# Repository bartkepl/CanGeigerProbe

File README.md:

# CanGeigerProbe
## Sonda promieniowania G-M z interfejsem CAN

Polowa sonda promieniowania jonizującego z miniaturową lampą Geigera-Müllera, komunikująca się cyfrowo przez **CAN 2.0B**. Zaprojektowana jako element rozproszonego systemu pomiarowego: wąska sonda cylindryczna w obudowie aluminiowej, jedno złącze M12, micropower, odporność EMC klasy przemysłowej.

> **Status:** schemat (6 arkuszy hierarchicznych) i layout PCB zakończone, pliki produkcyjne wygenerowane — przed zamówieniem prototypu. Firmware na etapie szkieletu bring-up.

Inspiracja: sondy Polon-Alfa (DPO-G, ZR-1) — jedna sonda, cyfrowe wyjście do jednostki nadrzędnej, wymienność lamp.

---

## Płytka

Render 3D aktualnego layoutu (KiCad 10, 4 warstwy, 86 × 29.9 mm, wycięcie pod złącze M12 na lewej krawędzi):

| Góra (TOP) | Dół (BOTTOM) |
|---|---|
|  |  |

Cała elektronika mieści się na jednej stronie; spód pozostaje niemal pusty — rezerwa na strefę HV (widoczny prostokąt creepage z pinami anody i lampy), pole lutownicze wyprowadzeń transformatora oraz uziemienie obudowy. Transformator flybacka jest **off-board** (skręcona para przewodów 4–6 cm).

---

## Najważniejsze cechy

- **Programowalne HV 350–550 V** — jedna sonda obsługuje wiele typów lamp, setpoint ustawiany przez CAN bez zmian sprzętowych.
- **Micropower** — pobór idle rzędu setek µA dzięki buckowi LT8606 (Iq 2.5 µA), MCU w Stop 2 i podwójnemu wybudzaniu (RTC + aktywność magistrali).
- **Flyback sterowany deterministycznie z MCU** — brak dedykowanego kontrolera PWM; TIM2 generuje burst, ADC mierzy HV, firmware zamyka pętlę bang-bang.
- **CAN 2.0B (29-bit ID)** z wybudzaniem na aktywność magistrali, 125 kbit/s – 1 Mbit/s.
- **Przełączalna terminacja CAN** — split 2×59 Ω + 4.7 nF załączany dwoma PhotoMOS-ami z GPIO (sonda na końcu linii vs. w środku, bez zwór).
- **Pomiar własnego poboru prądu** — INA186 A4 (G=200) + shunt 0.5 Ω, rozdzielczość ~2 µA/count; diagnostyka linii i weryfikacja budżetu mocy.
- **Zegar czasu rzeczywistego z podtrzymaniem** — MCP79410 + ogniwo MS621FE; kwarc 32.768 kHz służy też do kalibracji wewnętrznego MSI w STM32.
- **Wymienność lamp** — rezystor gaszący `R12` na PCB dobierany pod konkretną lampę.
- **Odporność EMC** — kaskadowa ochrona coarse→fine (GDT 3-elektrodowe / TVS / CMC / podwójne ferryty), testy IEC 61000-4-2/-4/-5.
- **Obudowa aluminiowa IP67**, złącze M12 5-pin A-coded (standard CANopen CiA 303-1).

---

## Specyfikacja

| Parametr | Wartość |
|----------|---------|
| Detektor bazowy | DOI-80 (~400 V) |
| Zakres HV | 350–550 V, programowalny |
| Wielkości mierzone | CPS/CPM, moc dawki, dawka skumulowana, prąd zasilania, alarmy progowe |
| Interfejs | CAN 2.0B (extended ID), 125k / 250k / 500k / 1 Mbit |
| Zasilanie | 7–32 V DC, wspólna masa (bez izolacji galwanicznej) |
| Pobór idle | ~200 µA @ 12 V |
| Pobór aktywny | ~3.7 mA @ 12 V (chwilowo), do ~20 mA przy TX CAN @ 7 V |
| Ochrona EMC | ESD ±8 kV, Burst ±2 kV, Surge ±2 kV |
| Złącze | M12 5-pin A-coded (1=Vin, 2=GND, 3=CAN_H, 4=CAN_L, 5=Earth) |
| PCB | 4 warstwy, 86 × 29.9 mm, grubość 1.59 mm |
| Obudowa | Aluminiowa cylindryczna Ø wewn. 25 mm, IP67 |

---

## Kompatybilne lampy G-M

Zmiana lampy = zmiana programowa HV + dobór rezystora gaszącego `R12`.

| Lampa | HV nom. | R12 (quench) | Uwaga |
|-------|---------|--------------|-------|
| **DOI-80** | ~400 V | **5.1 MΩ** | domyślna |
| SBM-20 / STS-5 | 400 V | 4.7 MΩ | drop-in z DOI-80 |
| SBM-19 | ~400 V | 5.1 MΩ | |
| J305 / M4011 | ~400 V | 4.7 MΩ | lampy chińskie |
| LND712 | 500 V | 10 MΩ | wymaga wyższego HV |

Rezystor HV w obudowie 1206 (HVC1206) — lutowany wg używanej lampy.

---

## Architektura

```
M12 Vin (7-32V) ─▶ Ochrona (GDT+TVS+ferryt) ─▶ shunt 0.5Ω ─▶ LT8606 buck ─▶ +5V ─┬─▶ ATA6561 (CAN)
                                                    │                              │
                                                 INA186 ─▶ ADC                     ├─▶ MCP1700 LDO ─▶ +3.3V ─▶ STM32L432
                                                                                   │                              │
                                                                                   │                     MCP79410 RTC + BT1
                                                                                   │
                                                                                   └─▶ Flyback (Q1 + T1 P18/11) ─▶ +HV
                                                                                                                    │
   Lampa G-M ◀─ R12 (quench) ◀─ dzielnik HV 1GΩ:1MΩ ◀─────────────────────────────────────────────────────────────┘
        │
        └─▶ dzielnik pojemnościowy ─▶ COMP1 (próg z DAC1) ─▶ LPTIM (zliczanie w Stop 2)
```

Kluczowa cecha: **wspólna masa** (star ground), izolacja zapewniona wyłącznie przez TVS/GDT; `Earth` (obudowa) oddzielona od `GND` sygnałowej i łączona tylko przez Y-cap 1 nF/2 kV. Flyback „śpi" i budzi się kilka razy na sekundę — stąd pobór na poziomie µA.

### Arkusze schematu

| Arkusz | Plik | Zawartość |
|--------|------|-----------|
| root | [geiger_probe.kicad_sch](pcb/geiger_probe.kicad_sch) | połączenia hierarchiczne |
| PWR | [pwr.kicad_sch](pcb/pwr.kicad_sch) | buck LT8606, LDO MCP1700, INA186, dzielnik VIN_SENSE |
| MCU | [mcu.kicad_sch](pcb/mcu.kicad_sch) | STM32L432, RTC MCP79410, kwarc 32k, SWD (Tag-Connect) |
| HV | [hv.kicad_sch](pcb/hv.kicad_sch) | flyback (trafo, Q1, snubber RCD), dzielnik HV, detektor GM + shaper |
| CAN_BUS | [can_bus.kicad_sch](pcb/can_bus.kicad_sch) | ATA6561, terminacja PhotoMOS |
| PROTECTION | [prot.kicad_sch](pcb/prot.kicad_sch) | ochrona Vin i CAN, złącze M12 |

Wyrenderowane PDF-y: [schemat](prod/sch/geiger_probe.pdf) · [PCB](prod/pcb/geiger_probe.pdf) · [interaktywny BOM](prod/ibom/geiger_probe_ibom.html).

---

## Kluczowe komponenty

| Blok | Element | Uwaga |
|------|---------|-------|
| Buck | LT8606IDC#TRPBF | DFN-8, Iq 2.5 µA (zawsze Burst Mode), Vref FB 0.778 V — jedyny element spoza TME |
| LDO 3.3 V | MCP1700-3302E/MB | SOT-89, Iq 1.6 µA |
| Current sense | INA186A4IDCKR + 0.5 Ω | 40 V CM, G=200, pin EN — pomiar poboru sondy |
| MCU | STM32L432KCU6 | bxCAN, LPTIM, COMP1, TIM2, ADC, DAC1 |
| RTC | MCP79410-I/MS + MS621FE-FL11E | RTC/EEPROM I2C z podtrzymaniem, kwarc 32.768 kHz |
| CAN | ATA6561-GAQW-N | zamiennik TJA1042 dostępny w TME |
| Terminacja CAN | 2× GAQY212GS + 2× 59 Ω + 4.7 nF | split przełączalny, sterowany BSS138 |
| Transformator | własny P18/11-3F3, 17:510 | nawijany ręcznie, off-board |
| Klucz flyback | DMN3404L | 30 V, snubber RCD (BAV21WS) clamp do +5 V |
| Dioda HV | STTH112A | 1200 V |
| Dzielnik HV | 2× HVC1206 500 MΩ | /1001, ochrona ADC diodami BAV199 |
| Ochrona Vin | 3R090-5S (GDT) + SMBJ33CA + PMEG6030EP + 2× SMBJ36A | kaskada coarse→fine, podwójny ferryt BLM31 |
| Ochrona CAN | 3R090-5S + CDSOT23-T24CAN + ACT45B-510 | GDT, dedykowany TVS, CMC |

Pełna lista: [prod/bom/](prod/bom/) (generowana z KiCad, nietrackowana w git). Szacunkowy koszt kompletu: **~160–200 zł**.

---

## Transformator (DIY)

Najbardziej „ręczna" część projektu — rdzeń kubełkowy **P18/11-3F3**, mocowany śrubą **M2 A2 (nierdzewna, niemagnetyczna!)** z podkładkami nylonowymi chroniącymi kruchy ferryt.

- Pierwotne: **17 zw** drut 0.30 mm CuL
- Wtórne: **510 zw** drut 0.10 mm CuL (przekładnia 1:30)
- Szczelina: Kapton 100 µm między połówkami
- Parametry docelowe: Lp ≈ 75 µH, Ls ≈ 67 mH, leakage < 1.5 µH, izolacja P/S > 1 GΩ

Zasilany z **+5 V** (nie z Vin), snubber RCD clamp do +5 V — recykling energii rozproszenia, Vds ~20 V, cichy EMC. Procedura nawijania, obliczenia i testy (hi-pot 1 kV/60 s) — patrz dokumentacja projektowa.

---

## Firmware

Projekt STM32CubeIDE w [firmware/CanGeigerProbe/](firmware/CanGeigerProbe/) — na razie szkielet wygenerowany z CubeMX ([CanGeigerProbe.ioc](firmware/CanGeigerProbe/CanGeigerProbe.ioc)) z inicjalizacją ADC1, CAN1, COMP1, DAC1, I2C1 i TIM2. Logika aplikacji (pętla HV, zliczanie w Stop 2, protokół CAN) do napisania.

---

## Roadmap

- [x] **Faza 1** — projekt: topologia, dobór komponentów, obliczenia, EMC, budżet mocy
- [ ] **Faza 2** — prototyp transformatora (nawinięcie, strojenie, testy)
- [x] **Faza 3** — schemat i layout PCB w KiCad (strefy HV / analog / cyfrowe), pliki produkcyjne wygenerowane
- [ ] **Faza 3b** — zamówienie PCB, montaż sekcyjny, bring-up sprzętowy
- [ ] **Faza 4** — firmware (LPTIM+COMP w Stop 2, pętla HV, bxCAN + wake-up, RTC/kalibracja MSI, current-sense, protokół)
- [ ] **Faza 5** — kalibracja HV per lampa, kalibracja CPS→µSv/h (Cs-137), testy EMC
- [ ] **Faza 6** — mechanika: obudowa Al, montaż M12, testy IP67

---

## Struktura repozytorium

```
.
├── media/          # rendery 3D płytki
├── pcb/            # projekt KiCad 10 (schemat hierarchiczny, PCB, biblioteki lokalne, modele 3D)
├── prod/           # pliki produkcyjne: gerbery (.zip), PDF schematu i PCB, interaktywny BOM
├── sim/            # symulacje LTspice (flyback HV, LT8606)
└── firmware/       # projekt STM32CubeIDE (STM32L432, szkielet bring-up)
```

Pliki produkcyjne generowane są jobsetami KiCad: [gen_prod.kicad_jobset](pcb/gen_prod.kicad_jobset) (PDF + BOM), [gen_gerber.kicad_jobset](pcb/gen_gerber.kicad_jobset) (gerbery + wiertła), [gen_media.kicad_jobset](pcb/gen_media.kicad_jobset) (rendery 3D).

---

## Referencje

- Analog Devices **CN-0536** — Geiger Counter Circuit (odczyt z anody, dzielnik pojemnościowy, komparator)
- STM32L432: RM0394, DS11453; bxCAN: AN2606, AN5028
- LT8606 (Analog Devices), MCP1700 / MCP79410 / ATA6561 (Microchip), INA186 (TI)
- Ferroxcube P18/11, materiał 3F3; EPCOS/TDK B65651/B65652
- IEC 61000-4-2/-4/-5; EN 61326-1; EN 61000-6-2
- CAN 2.0B: ISO 11898-1/-2; CANopen CiA 301, CiA 303-1; M12: IEC 61076-2-101
- Polski podręcznik metrologii promieniowania — układy pracy liczników DOI/BOI/GOI

---

## Licencja

MIT

---

> ⚠️ **Uwaga bezpieczeństwa:** urządzenie generuje napięcie ~350–550 V. Zachowaj ostrożność przy uruchamianiu i pomiarach obwodów HV.

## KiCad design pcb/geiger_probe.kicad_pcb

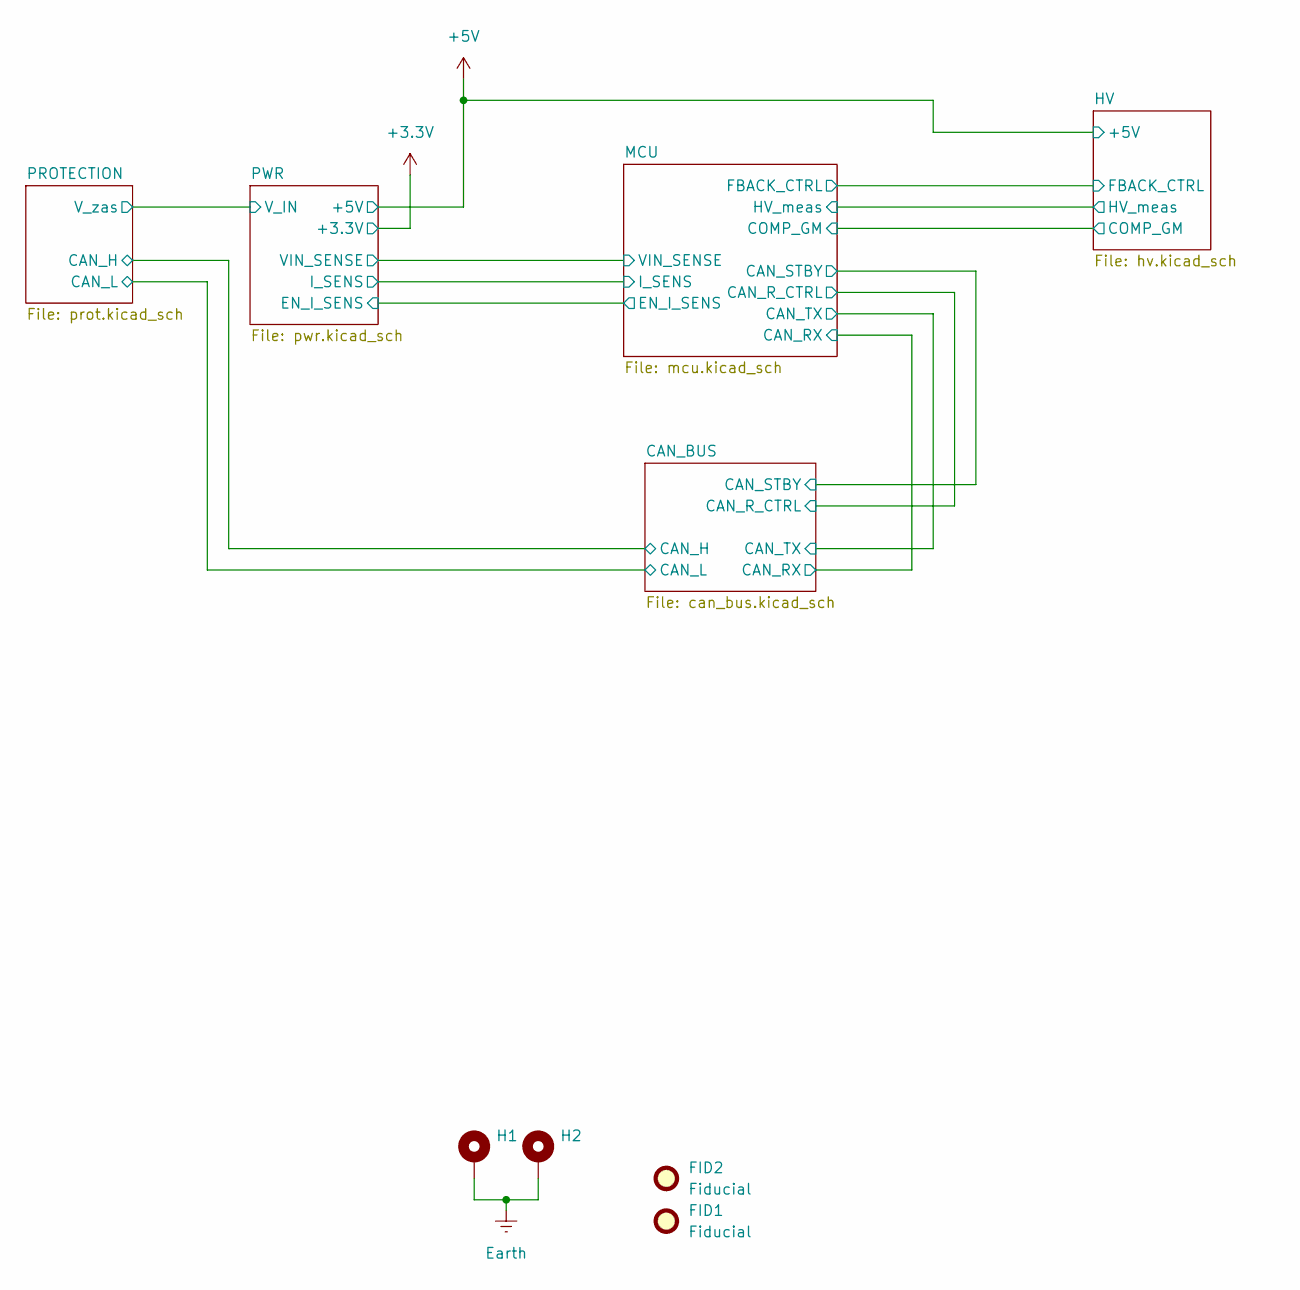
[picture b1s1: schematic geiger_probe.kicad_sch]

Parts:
FID1, FID2: Fiducial; Fiducial_0.5mm_Mask1mm
H1, H2: MountingHole_Pad; Sinhoo_SMTSO-M2_Hole3.8mm_Pad6.2mm

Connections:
Earth: H1.1 (1_1), H2.1 (1_1); also elsewhere on the board

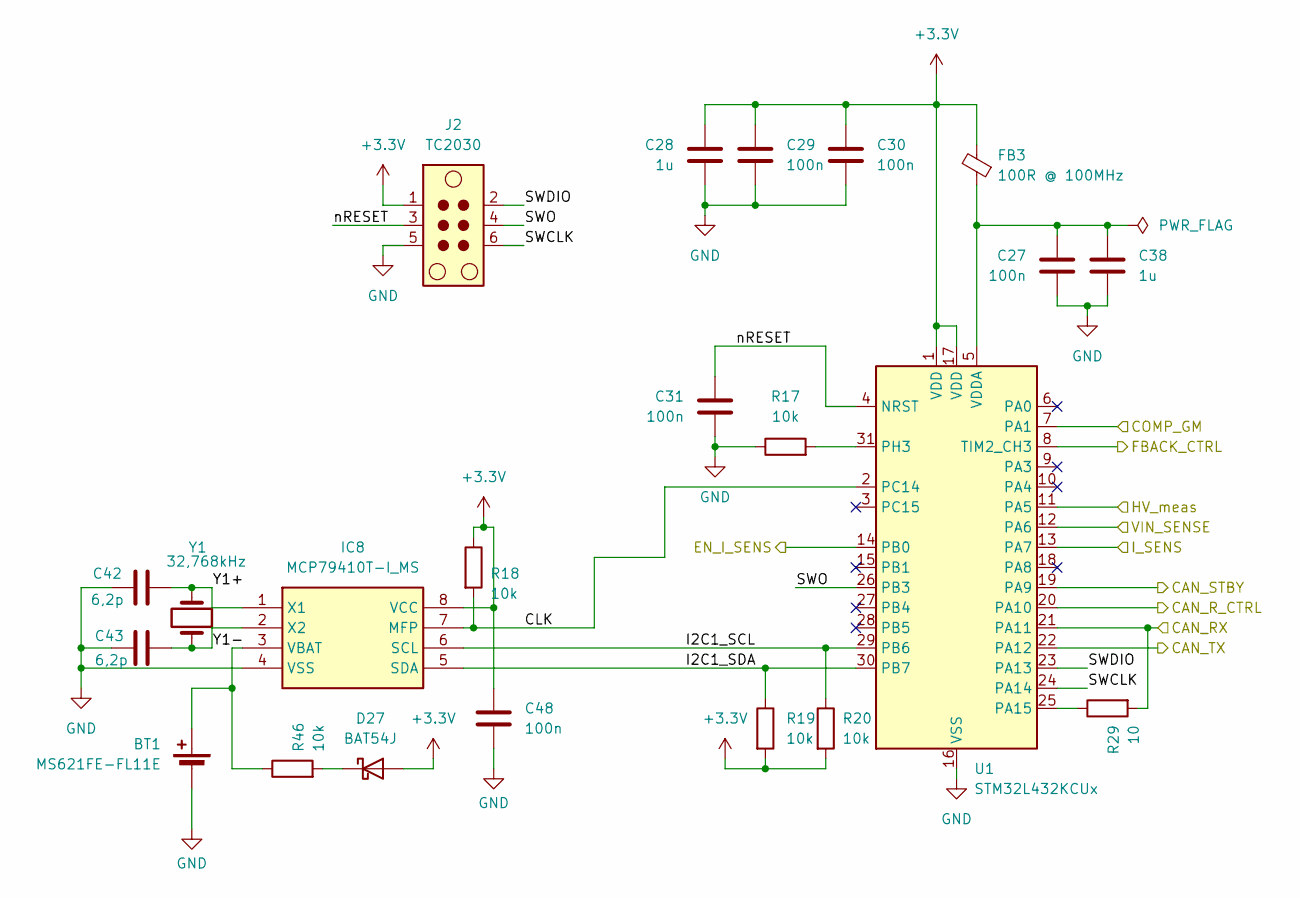
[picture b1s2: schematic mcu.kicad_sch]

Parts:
BT1: MS621FE-FL11E; BAT_MS621FE-FL11E; MPN MS621FE-FL11E
C27, C29, C30, C31, C48: 100n; C_0603_1608Metric; MPN TCC0603X7R104K500CT; LCSC C282519
C28, C38: 1u; C_0603_1608Metric; MPN 0603X105K500NT; LCSC C157684
C42, C43: 6,2p; C_0402_1005Metric; MPN CC0402CRNPO9BN6R2; LCSC C325456
D27: BAT54J; D_SOD-323F; MPN BAT54J,115
FB3: 100R @ 100MHz; L_0603_1608Metric; MPN MH1608-101Y
IC8: MCP79410T-I_MS; SOP65P490X110-8N; MPN MCP79410-I/MS
J2: TC2030; Tag-Connect_TC2030-IDC-NL_2x03_P1.27mm_Vertical
R17, R18, R19, R20, R46: 10k; R_0603_1608Metric; MPN RMS06FT1002; LCSC C209013
R29: 10; R_0603_1608Metric; MPN 0603WAF100JT5E; LCSC C22859
U1: STM32L432KCUx; QFN-32-1EP_5x5mm_P0.5mm_EP3.1x3.1mm_ThermalVias; MPN STM32L432KCU6
Y1: 32,768kHz; Crystal_SMD_MicroCrystal_CC7V-T1A-2Pin_3.2x1.5mm; MPN WTL1X80739BEL

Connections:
+3.3V: C28.1, C29.2, C30.2, C48.1, D27.2 (A), FB3.2, IC8.8 (VCC), J2.1, R18.1, R19.2, R20.2, U1.1 (VDD), U1.17 (VDD); also elsewhere on the board
/CAN_BUS/CAN_RX: R29.2, U1.21 (PA11); also elsewhere on the board
/CAN_BUS/CAN_R_CTRL: U1.20 (PA10); also elsewhere on the board
/CAN_BUS/CAN_STBY: U1.19 (PA9); also elsewhere on the board
/CAN_BUS/CAN_TX: U1.22 (PA12); also elsewhere on the board
/HV/COMP_GM: U1.7 (PA1); also elsewhere on the board
/HV/FBACK_CTRL: U1.8 (TIM2_CH3); also elsewhere on the board
/HV/HV_meas: U1.11 (PA5); also elsewhere on the board
/MCU/CLK: IC8.7 (MFP), R18.2, U1.2 (PC14)
/MCU/EN_I_SENS: U1.14 (PB0); also elsewhere on the board
/MCU/I2C1_SCL: IC8.6 (SCL), R20.1, U1.29 (PB6)
/MCU/I2C1_SDA: IC8.5 (SDA), R19.1, U1.30 (PB7)
/MCU/I_SENS: U1.13 (PA7); also elsewhere on the board
/MCU/SWCLK: J2.6, U1.24 (PA14)
/MCU/SWDIO: J2.2, U1.23 (PA13)
/MCU/SWO: J2.4, U1.26 (PB3)
/MCU/VIN_SENSE: U1.12 (PA6); also elsewhere on the board
/MCU/Y1+: C42.2, IC8.1 (X1), Y1.1
/MCU/Y1-: C43.2, IC8.2 (X2), Y1.2
/MCU/nRESET: C31.2, J2.3, U1.4 (NRST)
GND: BT1.2 (-), C27.1, C28.2, C29.1, C30.1, C31.1, C38.2, C42.1, C43.1, C48.2, IC8.4 (VSS), J2.5, R17.1, U1.16 (VSS), U1.32 (VSS), U1.33 (VSS); also elsewhere on the board
unnamed: BT1.1 (+), IC8.3 (VBAT), R46.1
unnamed: D27.1 (K), R46.2
unnamed: R29.1, U1.25 (PA15)
unnamed: R17.2, U1.31 (PH3)
unnamed: C27.2, C38.1, FB3.1, U1.5 (VDDA)

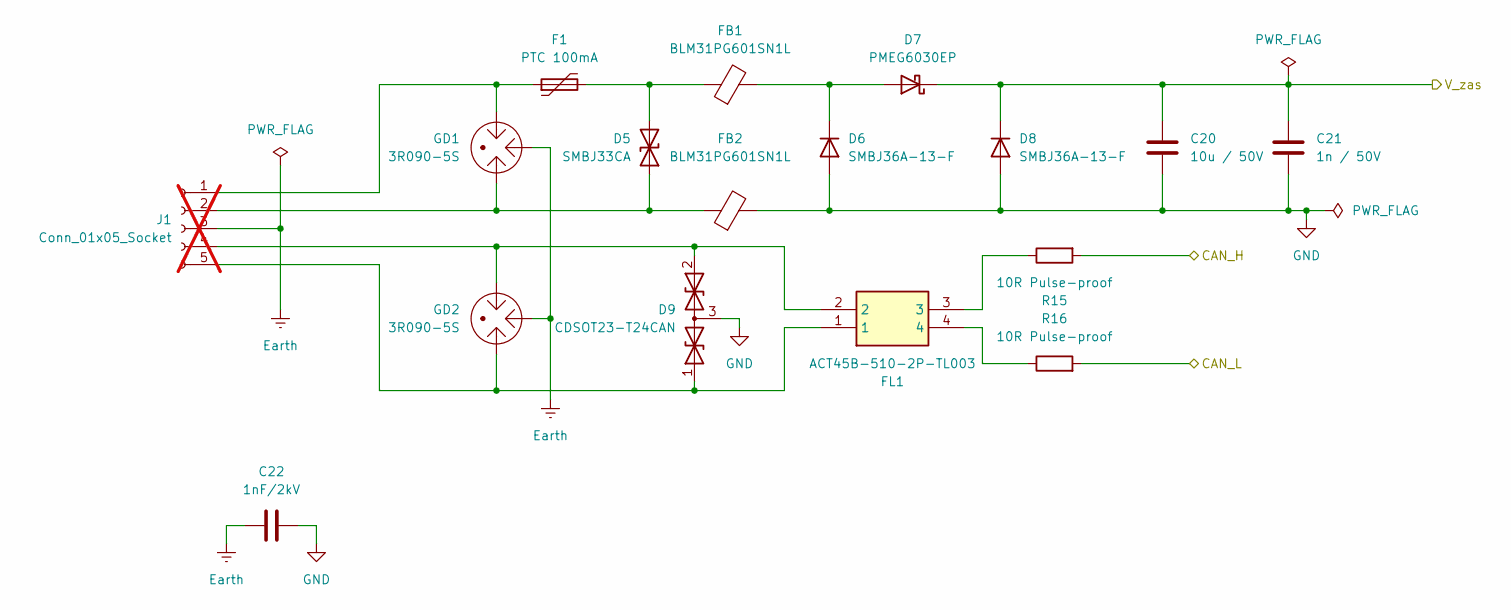
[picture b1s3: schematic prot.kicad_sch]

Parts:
C20: 10u / 50V; C_1206_3216Metric; MPN CS3216X5R106K500NRI; LCSC C513774
C21: 1n / 50V; C_0603_1608Metric; MPN CC0603JRNPO9BN102; LCSC C106246
C22: 1nF/2kV; C_1206_3216Metric; MPN C1206X102K202T; LCSC C106012
D5: SMBJ33CA; D_SMB; MPN SMBJ33CA
D6, D8: SMBJ36A-13-F; D_SMB; MPN SMBJ36A-13-F
D7: PMEG6030EP; D_SOD-128; MPN PMEG6030EP,115; Mouser 771-PMEG6030EP-115
D9: CDSOT23-T24CAN; TSOT-23; MPN CDSOT23-T24CAN; Mouser 652-CDSOT23-T24CAN
F1: PTC 100mA; Fuse_1206_3216Metric; MPN SN010-60
FB1, FB2: BLM31PG601SN1L; L_1206_3216Metric; MPN BLM31PG601SN1L
FL1: ACT45B-510-2P-TL003; ACT45B1012PTL003; MPN ACT45B-510-2P-TL003; LCSC C76584
GD1, GD2: 3R090-5S; 3R090A5S; MPN 3R090-5S; LCSC C782868
J1: Conn_01x05_Socket; PinHeader_1x05_P2.54mm_Vertical; not fitted
R15, R16: 10R Pulse-proof; R_1206_3216Metric; MPN RCA120610R0FKEA

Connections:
/CAN_BUS/CAN_H: R15.2; also elsewhere on the board
/CAN_BUS/CAN_L: R16.2; also elsewhere on the board
/PROTECTION/V_zas: C20.1, C21.2, D7.1 (K), D8.1 (K); also elsewhere on the board
Earth: C22.2, GD1.2, GD2.2, J1.3; also elsewhere on the board
GND: C20.2, C21.1, C22.1, D6.2 (A), D8.2 (A), D9.3 (common), FB2.2; also elsewhere on the board
unnamed: D5.1 (A1), FB2.1, GD1.3, J1.2
unnamed: D5.2 (A2), F1.2, FB1.1
unnamed: D6.1 (K), D7.2 (A), FB1.2
unnamed: D9.1 (A1), FL1.1, GD2.3, J1.5
unnamed: D9.2 (A2), FL1.2, GD2.1, J1.4
unnamed: FL1.3, R15.1
unnamed: FL1.4, R16.1
unnamed: F1.1, GD1.1, J1.1

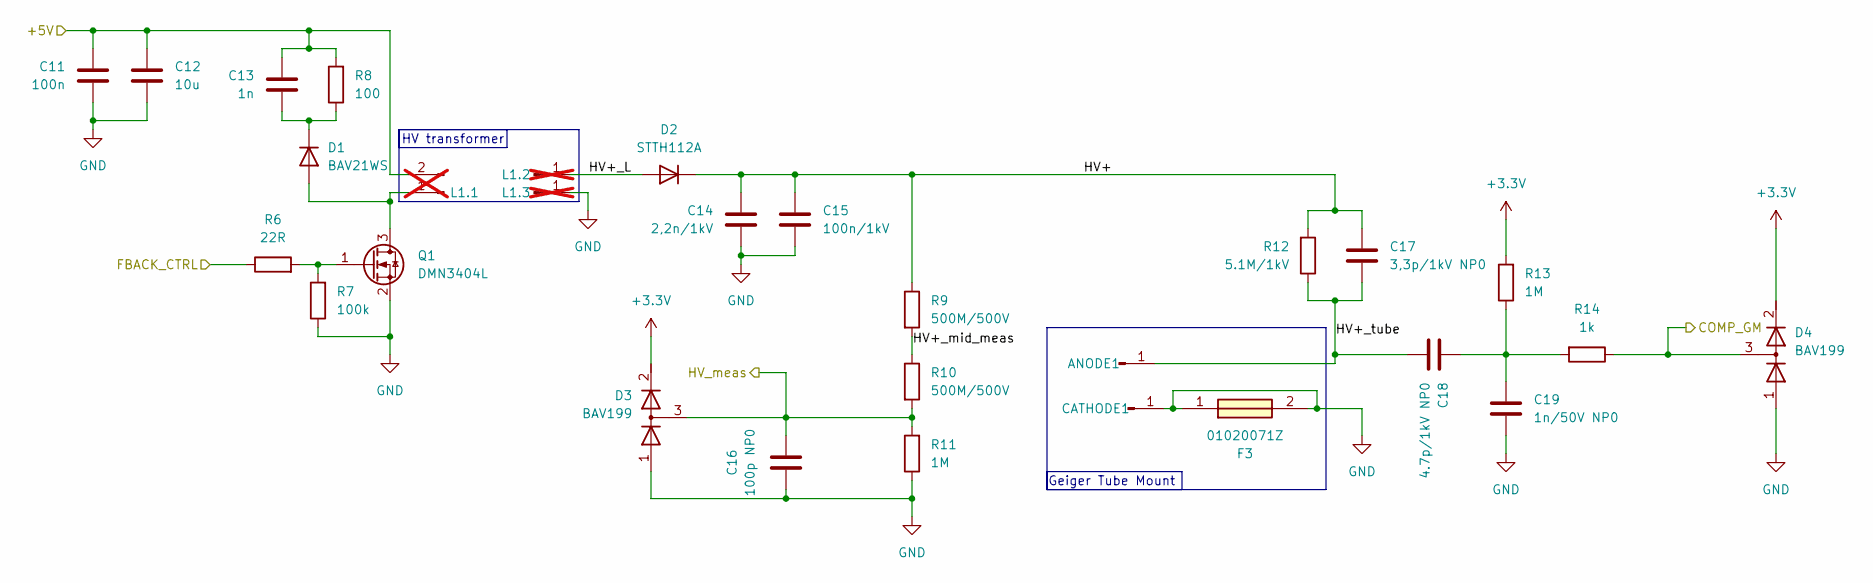
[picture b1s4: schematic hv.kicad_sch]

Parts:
ANODE1: Conn_01x01_Pin; PinHeader_1x01_P2.00mm_Vertical
C11: 100n; C_0603_1608Metric; MPN TCC0603X7R104K500CT; LCSC C282519
C12: 10u; C_1206_3216Metric; MPN CS3216X5R106K500NRI; LCSC C513774
C13: 1n; C_0603_1608Metric; MPN CC0603JRNPO9BN102; LCSC C106246
C14: 2,2n/1kV; C_1206_3216Metric; MPN TCC1206X7R222K102DTS; LCSC C344193
C15: 100n/1kV; C_1812_4532Metric; MPN NV1812B104K102CEMN; LCSC C780707
C16: 100p NP0; C_0603_1608Metric; MPN 0603N101J500CT; LCSC C335544
C17: 3,3p/1kV NP0; C_1206_3216Metric; MPN TCC1206COG3R0C102DT; LCSC C5449033
C18: 4.7p/1kV NP0; C_1206_3216Metric; MPN 1206N4R7C102CT; LCSC C2840257
C19: 1n/50V NP0; C_1206_3216Metric; MPN TCC1206COG102J500DT; LCSC C282783
CATHODE1: Conn_01x01_Pin; PinHeader_1x01_P2.00mm_Vertical
D1: BAV21WS; D_SOD-323F; MPN BAV21WS
D2: STTH112A; D_SMA; MPN STTH112A; LCSC C131297
D3, D4: BAV199; TSOT-23; MPN BAV199
F3: 01020071Z; MPN 01020071Z; Mouser 576-01020071Z
L1.1: Conn_01x02_Pin; PinHeader_1x02_P2.00mm_Vertical; not fitted
L1.2, L1.3: Conn_01x01_Pin; PinHeader_1x01_P2.00mm_Vertical; not fitted
Q1: DMN3404L; SOT-23; MPN DMN3404L-7; Mouser 621-DMN3404L-7
R6: 22R; R_0603_1608Metric; MPN 0603WAF220JT5E; LCSC C23345
R7: 100k; R_0603_1608Metric; MPN RC0603FR-07100KL; LCSC C14675
R8: 100; R_0603_1608Metric; MPN MR06X1000FTL; LCSC C327825
R9, R10: 500M/500V; R_1206_3216Metric; MPN HVCB1206JDD500M; Mouser 708-HVCB1206JDD500M
R11, R13: 1M; R_0603_1608Metric; MPN 0603WAF1004T5E; LCSC C22935
R12: 5.1M/1kV; R_1206_3216Metric; MPN HVC1206T5004JET; Mouser 588-HVC1206T5004JET
R14: 1k; R_0603_1608Metric; MPN RMS06FT1001; LCSC C209012

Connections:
+3.3V: D3.2 (K), D4.2 (K), R13.2; also elsewhere on the board
+5V: C11.2, C12.1, C13.2, L1.1.2, R8.2; also elsewhere on the board
/HV/COMP_GM: D4.3 (common), R14.1; also elsewhere on the board
/HV/FBACK_CTRL: R6.1; also elsewhere on the board
/HV/HV+: C14.1, C15.1, C17.1, D2.1 (K), R9.1, R12.2
/HV/HV+_L: D2.2 (A), L1.2.1 (Pin_1_1)
/HV/HV+_mid_meas: R9.2, R10.1
/HV/HV+_tube: ANODE1.1 (Pin_1_1), C17.2, C18.2, R12.1
/HV/HV_meas: C16.1, D3.3 (common), R10.2, R11.2; also elsewhere on the board
GND: C11.1, C12.2, C14.2, C15.2, C16.2, C19.2, CATHODE1.1 (Pin_1_1), D3.1 (A), D4.1 (A), F3.1, F3.2, L1.3.1 (Pin_1_1), Q1.2 (S), R7.1, R11.1; also elsewhere on the board
unnamed: C18.1, C19.1, R13.1, R14.2
unnamed: D1.2 (A), L1.1.1, Q1.3 (D)
unnamed: C13.1, D1.1 (K), R8.1
unnamed: Q1.1 (G), R6.2, R7.2

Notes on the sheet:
Geiger Tube Mount
HV transformer

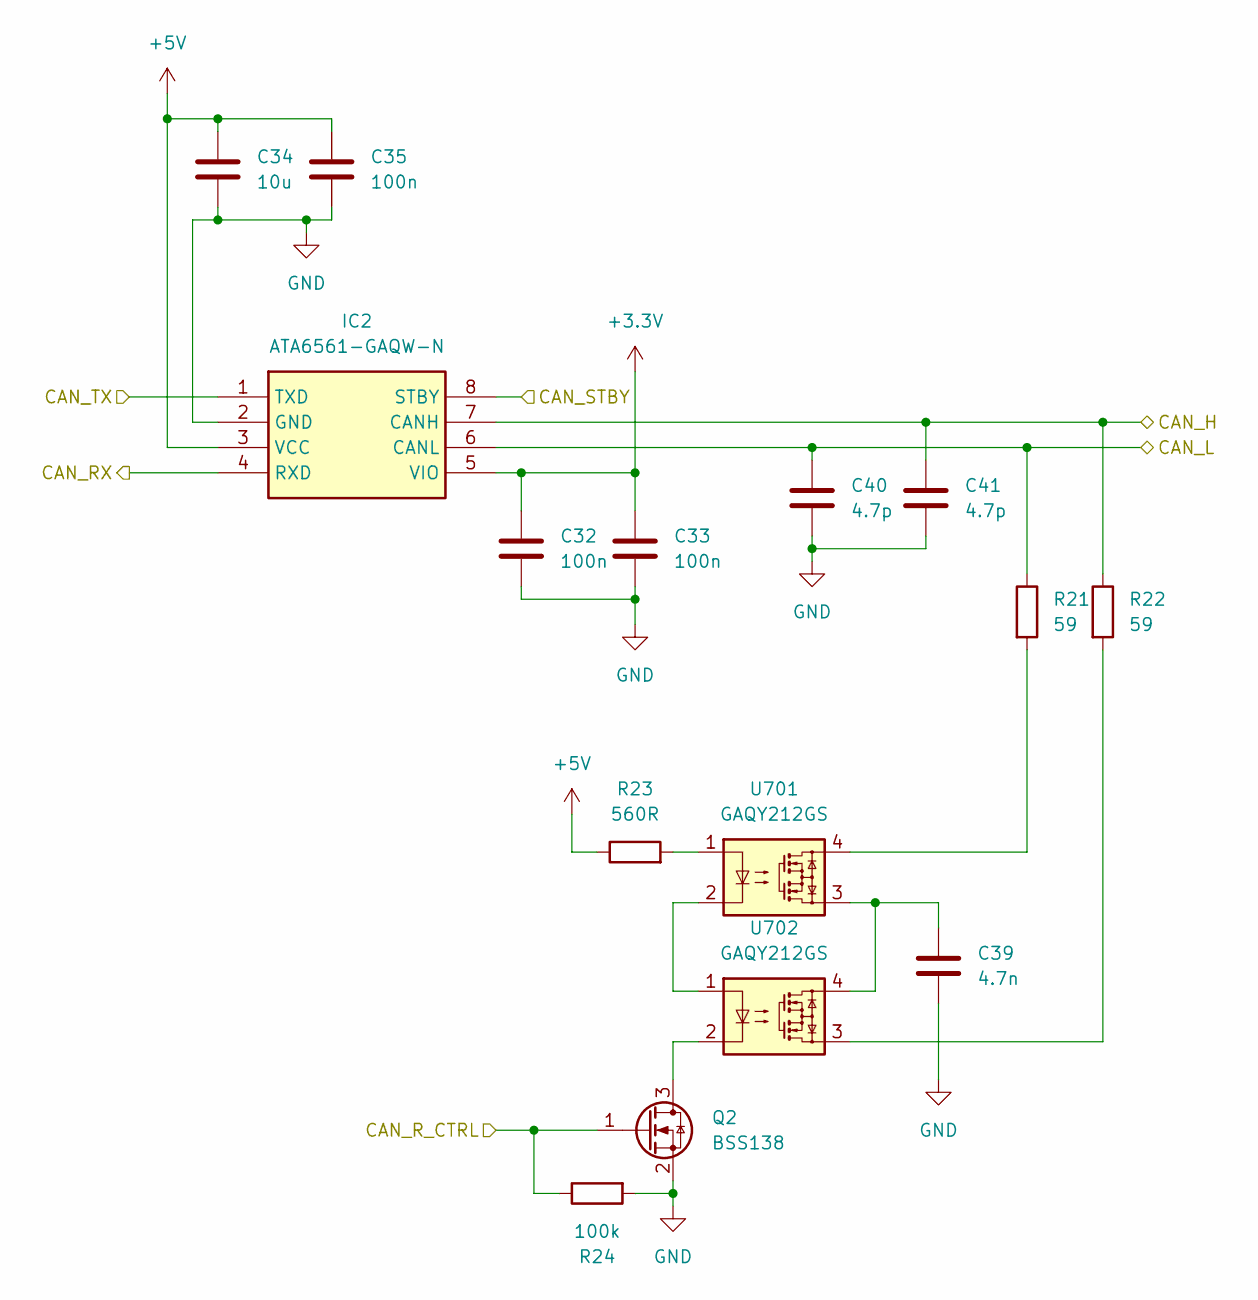
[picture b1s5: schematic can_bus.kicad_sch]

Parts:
C32, C33, C35: 100n; C_0603_1608Metric; MPN TCC0603X7R104K500CT; LCSC C282519
C34: 10u; C_1206_3216Metric; MPN CS3216X5R106K500NRI; LCSC C513774
C39: 4.7n; C_0603_1608Metric; MPN C1608C0G1H472JT000N; LCSC C342963
C40, C41: 4.7p; C_0603_1608Metric; MPN TCC0603COG4R7C500CT; LCSC C282506
IC2: ATA6561-GAQW-N; SOIC127P600X175-8N; MPN ATA6561-GAQW-N; Mouser 579-ATA6561-GAQW-N
Q2: BSS138; SOT-23; MPN BSS138; LCSC C112239
R21, R22: 59; R_0603_1608Metric; MPN RC0603FR-0759RL; LCSC C273801
R23: 560R; R_0603_1608Metric; MPN RS-03K5600FT; LCSC C136586
R24: 100k; R_0603_1608Metric; MPN RC0603FR-07100KL; LCSC C14675
U701, U702: GAQY212GS; SOP-4_3.8x4.1mm_P2.54mm; MPN GAQY212GS; LCSC C7435107

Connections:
+3.3V: C32.1, C33.1, IC2.5 (VIO); also elsewhere on the board
+5V: C34.1, C35.1, IC2.3 (VCC), R23.1; also elsewhere on the board
/CAN_BUS/CAN_H: C41.1, IC2.7 (CANH), R22.1; also elsewhere on the board
/CAN_BUS/CAN_L: C40.1, IC2.6 (CANL), R21.1; also elsewhere on the board
/CAN_BUS/CAN_RX: IC2.4 (RXD); also elsewhere on the board
/CAN_BUS/CAN_R_CTRL: Q2.1 (G), R24.1; also elsewhere on the board
/CAN_BUS/CAN_STBY: IC2.8 (STBY); also elsewhere on the board
/CAN_BUS/CAN_TX: IC2.1 (TXD); also elsewhere on the board
GND: C32.2, C33.2, C34.2, C35.2, C39.2, C40.2, C41.2, IC2.2 (GND), Q2.2 (S), R24.2; also elsewhere on the board
unnamed: C39.1, U701.3, U702.4
unnamed: Q2.3 (D), U702.2
unnamed: R21.2, U701.4
unnamed: R22.2, U702.3
unnamed: R23.2, U701.1
unnamed: U701.2, U702.1

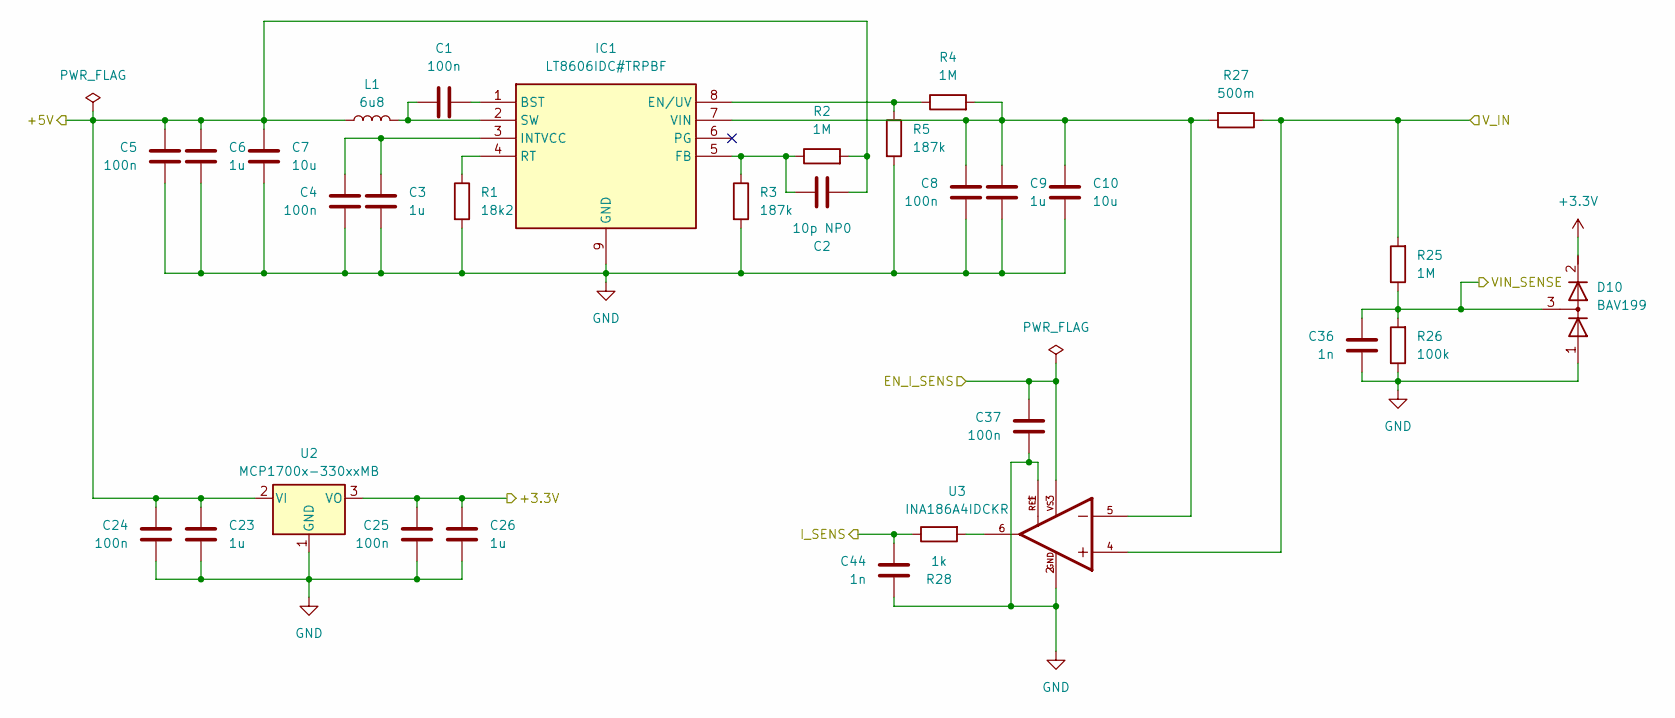
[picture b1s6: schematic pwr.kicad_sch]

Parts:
C1, C4, C5, C8, C24, C25, C37: 100n; C_0603_1608Metric; MPN TCC0603X7R104K500CT; LCSC C282519
C2: 10p NP0; C_0603_1608Metric; MPN CC0603JRNPO9BN100; LCSC C106245
C3, C6, C9, C23, C26: 1u; C_0603_1608Metric; MPN 0603X105K500NT; LCSC C157684
C7, C10: 10u; C_1206_3216Metric; MPN CS3216X5R106K500NRI; LCSC C513774
C36, C44: 1n; C_0603_1608Metric; MPN CC0603JRNPO9BN102; LCSC C106246
D10: BAV199; TSOT-23; MPN BAV199
IC1: LT8606IDC#TRPBF; SON45P200X200X80-9N-D; MPN LT8606IDC#TRMPBF; Mouser 584-LT8606IDCTRMPBF
L1: 6u8; L_1210_3225Metric; MPN LQH32PN6R8NN0L
R1: 18k2; R_0603_1608Metric; MPN 0603WAF1822T5E; LCSC C22892
R2, R4, R25: 1M; R_0603_1608Metric; MPN 0603WAF1004T5E; LCSC C22935
R3, R5: 187k; R_0603_1608Metric; MPN RTT031873FTP; LCSC C103367
R26: 100k; R_0603_1608Metric; MPN RC0603FR-07100KL; LCSC C14675
R27: 500m; R_0603_1608Metric; MPN SCR0603FR500; LCSC C3016460
R28: 1k; R_0603_1608Metric; MPN RMS06FT1001; LCSC C209012
U2: MCP1700x-330xxMB; SOT-89-3; MPN MCP1700T-3302E/MB
U3: INA186A4IDCKR; SOT65P210X110-6N; PARTREV B; LCSC C2878841

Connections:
+3.3V: C25.2, C26.1, D10.2 (K), U2.3 (VO); also elsewhere on the board
+5V: C2.1, C5.2, C6.1, C7.1, C23.1, C24.2, L1.1, R2.2, U2.2 (VI); also elsewhere on the board
/MCU/EN_I_SENS: C37.2, U3.3; also elsewhere on the board
/MCU/I_SENS: C44.2, R28.1; also elsewhere on the board
/MCU/VIN_SENSE: C36.2, D10.3 (common), R25.1, R26.2; also elsewhere on the board
/PROTECTION/V_zas: R25.2, R27.1, U3.4; also elsewhere on the board
GND: C3.2, C4.1, C5.1, C6.2, C7.2, C8.1, C9.2, C10.2, C23.2, C24.1, C25.1, C26.2, C36.1, C37.1, C44.1, D10.1 (A), IC1.9 (GND), R1.2, R3.2, R5.2, R26.1, U2.1 (GND), U3.1, U3.2; also elsewhere on the board
unnamed: C1.2, IC1.1 (BST)
unnamed: IC1.8 (EN/UV), R4.1, R5.1
unnamed: C2.2, IC1.5 (FB), R2.1, R3.1
unnamed: C3.1, C4.2, IC1.3 (INTVCC)
unnamed: IC1.4 (RT), R1.1
unnamed: C1.1, IC1.2 (SW), L1.2
unnamed: C8.2, C9.1, C10.1, IC1.7 (VIN), R4.2, R27.2, U3.5
unnamed: R28.2, U3.6

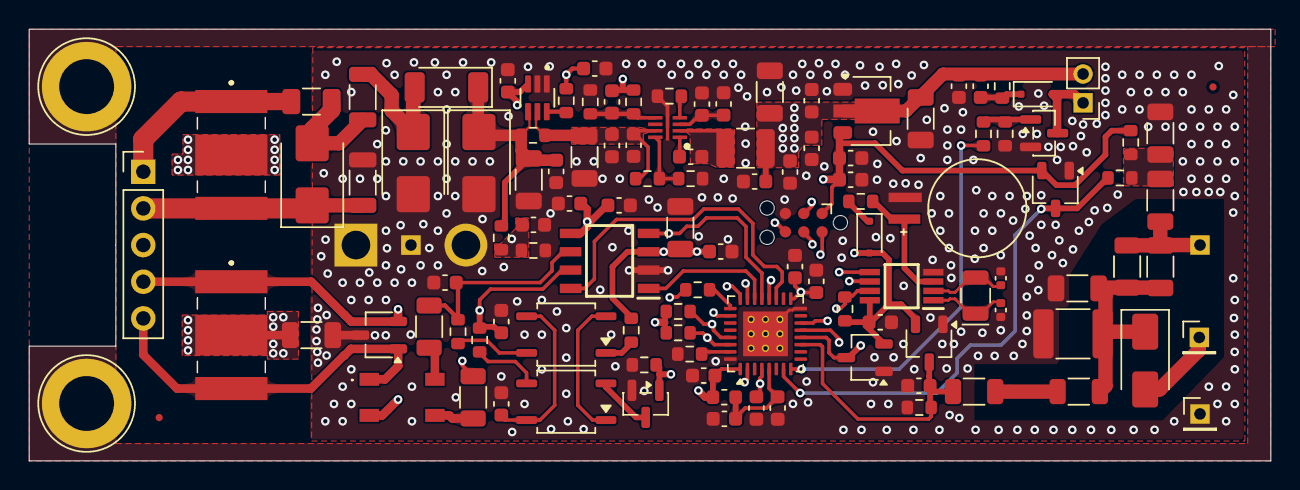
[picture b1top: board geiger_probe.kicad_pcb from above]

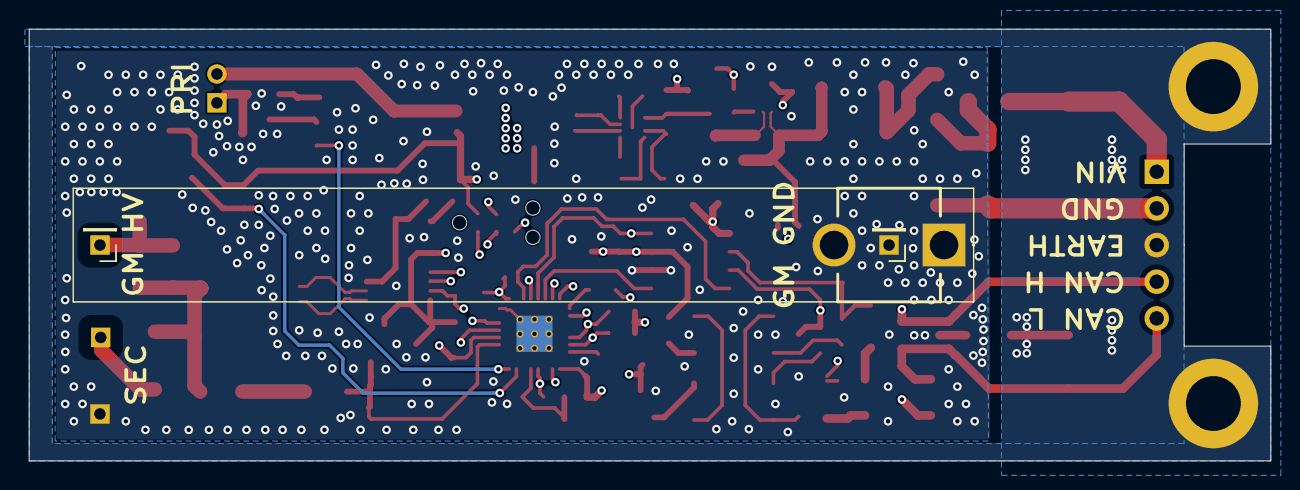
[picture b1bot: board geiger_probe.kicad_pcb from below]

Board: 4 copper layers, 86.0 x 29.9 mm, 118 parts (3 on the bottom side), 61 nets.

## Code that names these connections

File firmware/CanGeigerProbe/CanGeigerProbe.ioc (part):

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Mcu.Name=STM32L432K(B-C)Ux
Mcu.Package=UFQFPN32
Mcu.UserName=STM32L432KCUx
PA1.GPIOParameters=GPIO_Label
PA1.GPIO_Label=COMP_GM_IN
PA1.Mode=INP
PA1.Signal=COMP1_INP
PA10.GPIOParameters=GPIO_Label
PA10.GPIO_Label=CAN_R_CTRL
PA10.Signal=GPIO_Output
PA11.Mode=CAN_Activate
PA11.Signal=CAN1_RX
PA12.Mode=CAN_Activate
PA12.Signal=CAN1_TX
PA13\ (JTMS-SWDIO).GPIOParameters=GPIO_Label
PA13\ (JTMS-SWDIO).GPIO_Label=SWDIO
PA13\ (JTMS-SWDIO).Mode=Trace_Asynchronous_SW
PA13\ (JTMS-SWDIO).Signal=SYS_JTMS-SWDIO
PA14\ (JTCK-SWCLK).GPIOParameters=GPIO_Label
PA14\ (JTCK-SWCLK).GPIO_Label=SWCLK
PA14\ (JTCK-SWCLK).Mode=Trace_Asynchronous_SW
PA14\ (JTCK-SWCLK).Signal=SYS_JTCK-SWCLK
PA15\ (JTDI).GPIOParameters=GPIO_Label
PA15\ (JTDI).GPIO_Label=CAN_RX_IT
PA15\ (JTDI).Signal=GPXTI15
PA2.GPIOParameters=GPIO_Label
PA2.GPIO_Label=FBACK_CTRL
PA2.Signal=S_TIM2_CH3
PA5.GPIOParameters=GPIO_Label
PA5.GPIO_Label=HV_meas
PA5.Signal=ADCx_IN10
PA6.GPIOParameters=GPIO_Label
PA6.GPIO_Label=VIN_SENSE
PA6.Signal=ADCx_IN11
PA7.GPIOParameters=GPIO_Label
PA7.GPIO_Label=I_SENS
PA7.Signal=ADCx_IN12
PA9.GPIOParameters=GPIO_Label
PA9.GPIO_Label=CAN_STBY
PA9.Signal=GPIO_Output
PB0.GPIOParameters=GPIO_Label
PB0.GPIO_Label=EN_I_SENS
PB0.Signal=GPIO_Output
PB3\ (JTDO-TRACESWO).GPIOParameters=GPIO_Label
PB3\ (JTDO-TRACESWO).GPIO_Label=SWO
PB3\ (JTDO-TRACESWO).Mode=Trace_Asynchronous_SW
PB3\ (JTDO-TRACESWO).Signal=SYS_JTDO-SWO
PB6.Mode=I2C
PB6.Signal=I2C1_SCL
PB7.Mode=I2C
PB7.Signal=I2C1_SDA
RCC.HSE_VALUE=8000000
RCC.SYSCLKFreq_VALUE=2000000
board=custom
